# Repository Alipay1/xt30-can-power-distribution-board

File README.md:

# xt30-can-power-distribution-board

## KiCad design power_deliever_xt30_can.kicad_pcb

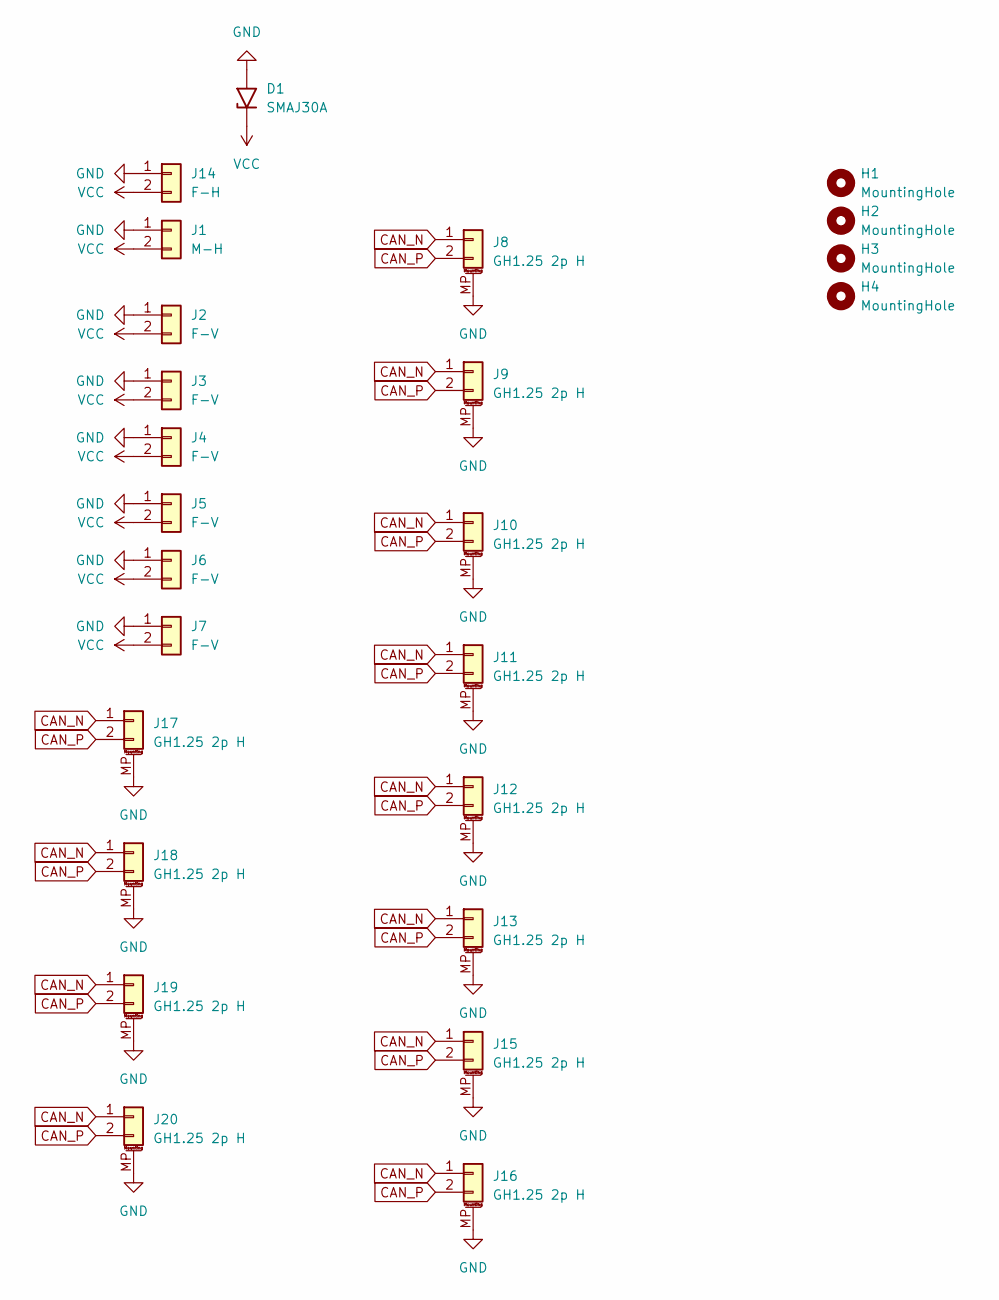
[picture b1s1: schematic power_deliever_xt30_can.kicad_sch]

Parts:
D1: SMAJ30A; D_SMA
H1, H2, H3, H4: MountingHole; MountingHole_2.7mm_M2.5_ISO7380
J1: M-H; AMASS_XT30PW-M_1x02_P2.50mm_Horizontal
J2, J3, J4, J5, J6, J7: F-V; AMASS_XT30U-F_1x02_P5.0mm_Vertical
J8, J9, J10, J11, J12, J13, J15, J16: GH1.25 2p H; JST_GH_SM02B-GHS-TB_1x02-1MP_P1.25mm_Horizontal
J14: F-H; AMASS_XT30PW-F_1x02_P2.50mm_Horizontal
J17, J18, J19, J20: GH1.25 2p H; JST_GH_BM02B-GHS-TBT_1x02-1MP_P1.25mm_Vertical

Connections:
CAN_N: J8.1, J9.1, J10.1, J11.1, J12.1, J13.1, J15.1, J16.1, J17.1, J18.1, J19.1, J20.1
CAN_P: J8.2, J9.2, J10.2, J11.2, J12.2, J13.2, J15.2, J16.2, J17.2, J18.2, J19.2, J20.2
GND: D1.2 (A2), J1.1, J2.1, J3.1, J4.1, J5.1, J6.1, J7.1, J8.MP (MountPin), J9.MP (MountPin), J10.MP (MountPin), J11.MP (MountPin), J12.MP (MountPin), J13.MP (MountPin), J14.1, J15.MP (MountPin), J16.MP (MountPin), J17.MP (MountPin), J18.MP (MountPin), J19.MP (MountPin), J20.MP (MountPin)
VCC: D1.1 (A1), J1.2, J2.2, J3.2, J4.2, J5.2, J6.2, J7.2, J14.2

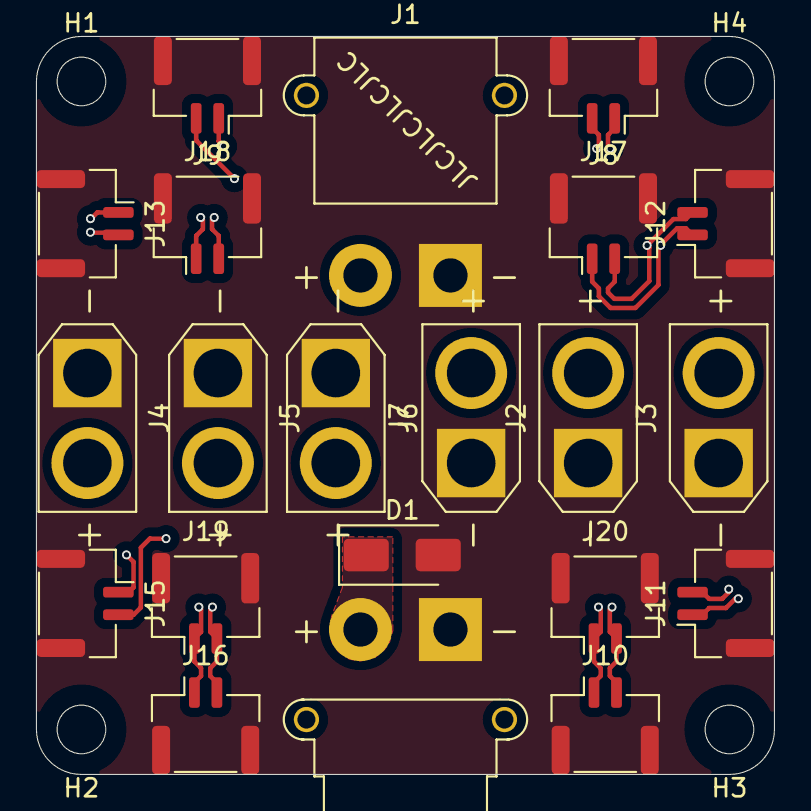
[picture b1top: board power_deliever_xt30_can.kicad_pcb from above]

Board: 4 copper layers, 41.0 x 41.0 mm, 25 parts (0 on the bottom side), 4 nets.
